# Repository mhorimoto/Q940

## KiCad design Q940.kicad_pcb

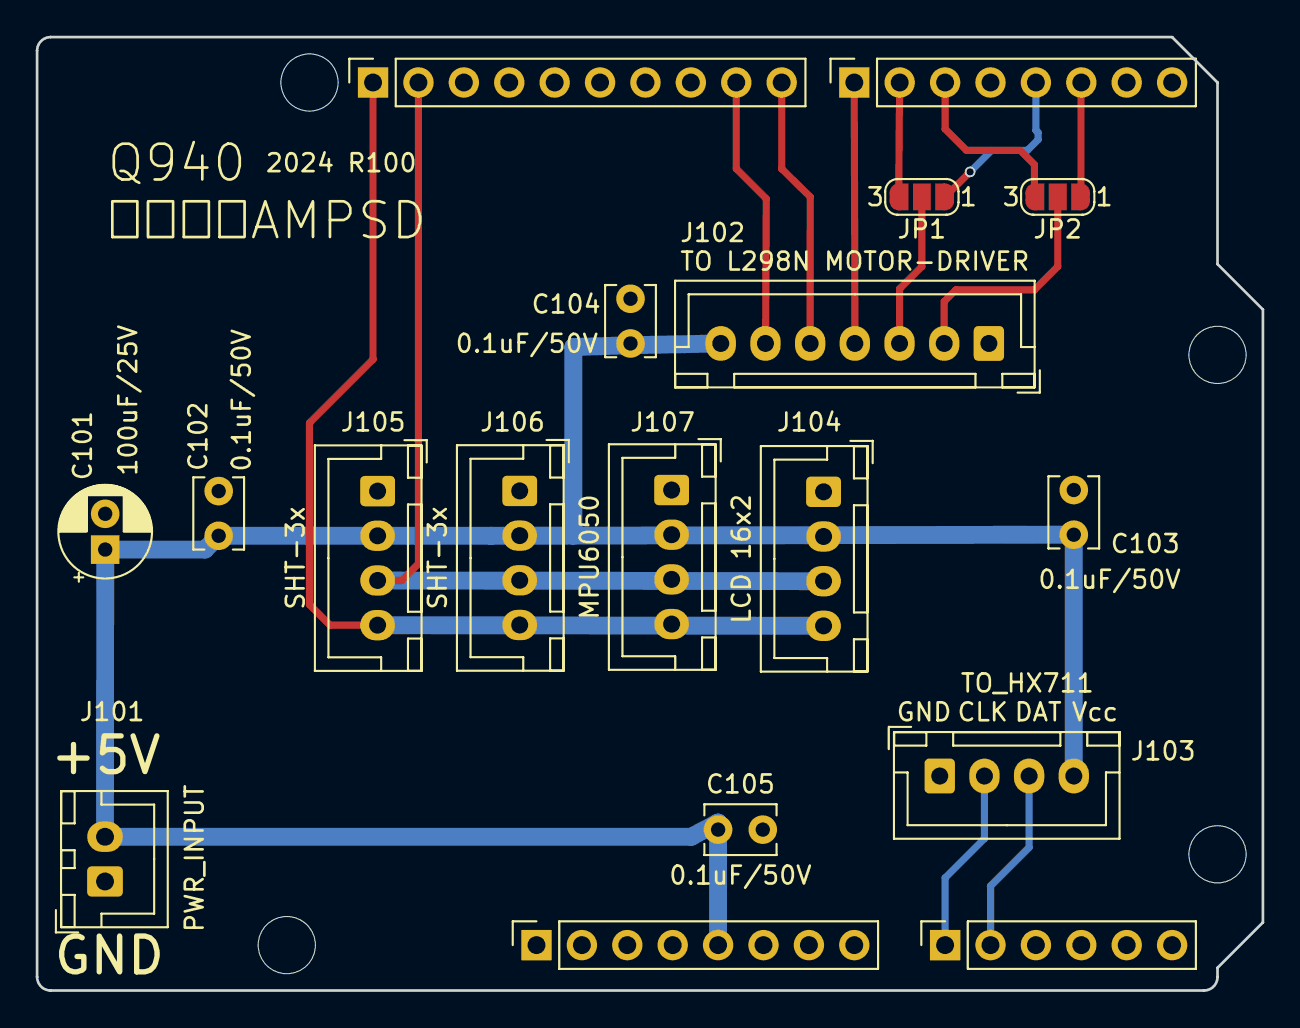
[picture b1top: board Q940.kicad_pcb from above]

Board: 2 copper layers, 68.6 x 53.3 mm, 22 parts (0 on the bottom side), 15 nets.

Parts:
C101: 100uF/25V; CP_Radial_D5.0mm_P2.00mm
C102, C103, C104, C105: 0.1uF/50V; C_Disc_D3.8mm_W2.6mm_P2.50mm
J1: Power; PinSocket_1x08_P2.54mm_Vertical
J2: Digital/PWM; PinSocket_1x10_P2.54mm_Vertical
J3: Analog; PinSocket_1x06_P2.54mm_Vertical
J4: Digital/PWM; PinSocket_1x08_P2.54mm_Vertical
J101: PWR_INPUT; JST_XH_B2B-XH-A_1x02_P2.50mm_Vertical
J102: TO L298N MOTOR-DRIVER; JST_XH_B7B-XH-A_1x07_P2.50mm_Vertical
J103: TO_HX711; JST_XH_B4B-XH-A_1x04_P2.50mm_Vertical
J104: LCD 16x2; JST_XH_B4B-XH-A_1x04_P2.50mm_Vertical
J105, J106: SHT-3x; JST_XH_B4B-XH-A_1x04_P2.50mm_Vertical
J107: MPU6050; JST_XH_B4B-XH-A_1x04_P2.50mm_Vertical
JP1: STOP1_SW; SolderJumper-3_P1.3mm_Open_RoundedPad1.0x1.5mm_NumberLabels
JP2: STOP2_SW; SolderJumper-3_P1.3mm_Open_RoundedPad1.0x1.5mm_NumberLabels
MH1, MH2, MH3, MH4: MountingHole_3.2mm

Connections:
+5V: C101.1, C102.1, C103.1, C104.1, C105.1, J1.5, J101.2, J102.7, J103.4, J104.2, J105.2, J106.2, J107.2
/2: J4.6, JP2.1 (A)
/7: J4.1, J102.4
/8: J2.10, J102.5
/*3: J4.5, JP1.1 (A)
/*5: J4.3, JP2.3 (B)
/*6: J4.2, JP1.3 (B)
/*9: J2.9, J102.6
/A0: J3.1, J103.2
/A1: J3.2, J103.3
/SCL/A5: J2.1, J3.6, J104.4, J105.4, J106.4, J107.4
/SDA/A4: J2.2, J3.5, J104.3, J105.3, J106.3, J107.3
GND: C101.2, C102.2, C103.2, C104.2, C105.2, J1.6, J1.7, J2.4, J101.1, J102.1, J103.1, J104.1, J105.1, J106.1, J107.1
unnamed: J102.2, JP2.2 (C)
unnamed: J102.3, JP1.2 (C)

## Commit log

2024-05-26 とりあえずリリース
2024-06-04 change Arduino Shield pin
2024-06-05 append MPU6050 and Hardware interruption
2024-06-05 remove 1N4007
